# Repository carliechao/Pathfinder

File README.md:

# Pathfinder - Memory Game
starter project and my first repo
this project is a game that tests your memory by playing leds in sequence and having you to repeat the pattern!

A little into the motivation of why I started this project was because I was interested in robotics but never designed anything myself. I had taken note of hackclub for a while but never decided to actually undertake in any of the programs until one day... My friends and I saw how grim our college apps were at the end of 11th grade and decided soemthing had to be done. To be brief, nothing was done. But I did not want to extinguish the light of the motivation just yet and continued with my project. Some of my disdain is echoed into the memory game where you continously fight the overwhelming torrent of forgetfulness by strengthening your mental fortitude through a trial of memory. 

Similar to the challenge that this memory game presents, the process of designing the board also took had lots of challenges I had to overcome and learn from. I learnt, for example, how to draw schematics, lay out my pcb, and code the thing. I am excited to finally finish up this project and see where this experience will take me next.

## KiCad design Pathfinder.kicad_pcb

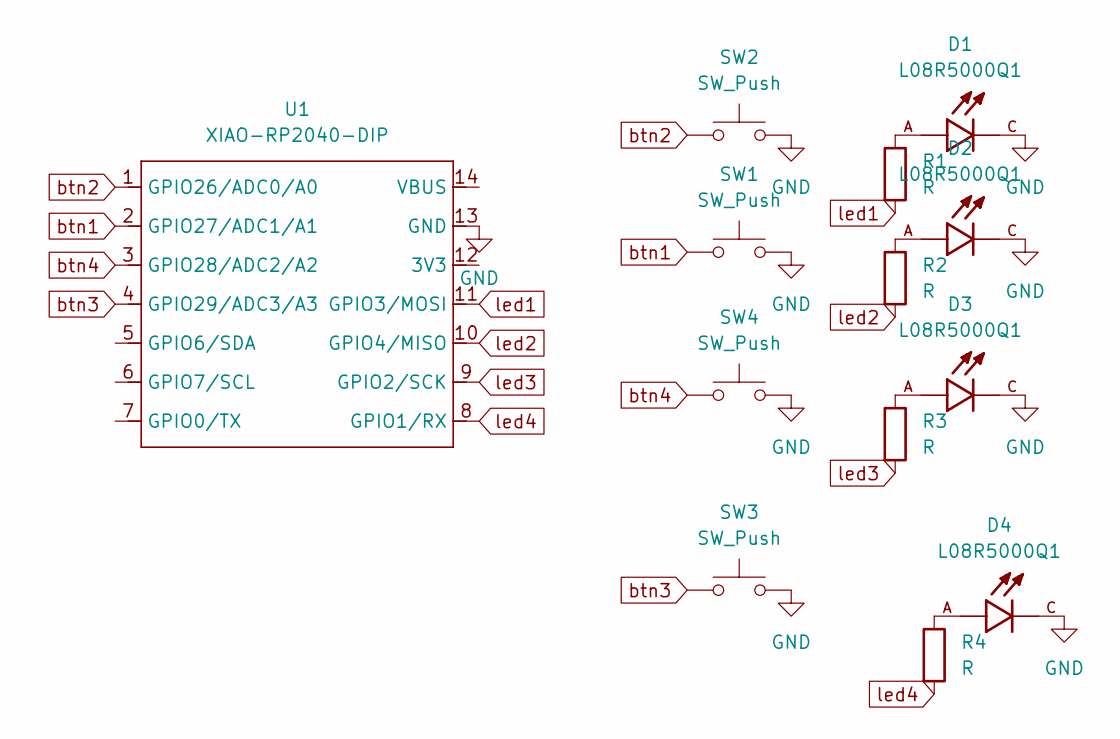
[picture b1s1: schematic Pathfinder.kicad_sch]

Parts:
D1, D2, D3, D4: L08R5000Q1; LEDRD254W57D500H1070; PARTREV NA
R1, R2, R3, R4: R; R_Axial_DIN0207_L6.3mm_D2.5mm_P7.62mm_Horizontal
SW1, SW2, SW3, SW4: SW_Push; SW_Cherry_MX_1.00u_PCB
U1: XIAO-RP2040-DIP

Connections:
GND: D1.C, D2.C, D3.C, D4.C, SW1.2, SW2.2, SW3.2, SW4.2, U1.13 (GND)
unnamed: D1.A, R1.1
unnamed: D2.A, R2.1
unnamed: D3.A, R3.1
unnamed: D4.A, R4.1
btn1: SW1.1, U1.2 (GPIO27/ADC1/A1)
btn2: SW2.1, U1.1 (GPIO26/ADC0/A0)
btn3: SW3.1, U1.4 (GPIO29/ADC3/A3)
btn4: SW4.1, U1.3 (GPIO28/ADC2/A2)
led1: R1.2, U1.11 (GPIO3/MOSI)
led2: R2.2, U1.10 (GPIO4/MISO)
led3: R3.2, U1.9 (GPIO2/SCK)
led4: R4.2, U1.8 (GPIO1/RX)

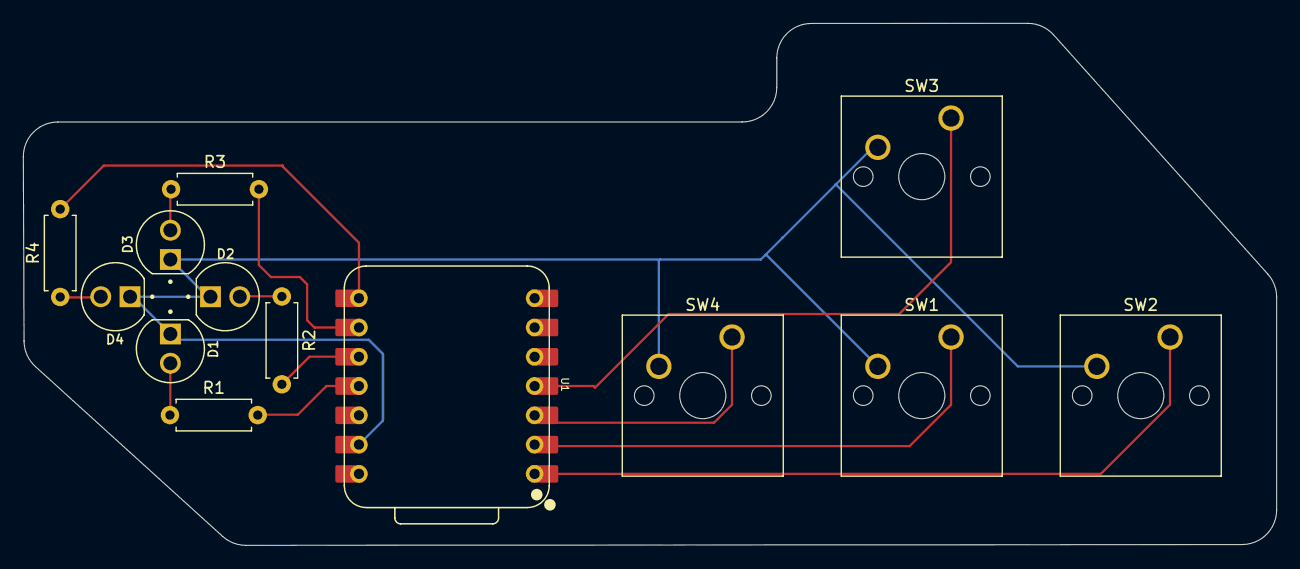
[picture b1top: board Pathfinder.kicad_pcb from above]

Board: 2 copper layers, 108.7 x 45.3 mm, 13 parts (0 on the bottom side), 13 nets.

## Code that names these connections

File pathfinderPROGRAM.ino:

int btns[] = {D1,D0,D3,D2};
int btnsLength = sizeof(btns)/sizeof(btns[0]);
int leds[] = {D10,D9,D8,D7};
int ledsLength = sizeof(leds)/sizeof(leds[0]);
// int led1 = D10;
// int led2 = D9;
// int led3 = D8;
// int led4 = D7;

void setup() {

  for (int i = 0; i < btnsLength; i++){
    pinMode(btns[i], INPUT_PULLUP);
  }

  for (int i = 0; i < ledsLength ; i++){
    pinMode(leds[i], OUTPUT);
  }

  //set a random seed so random is not predictable
  randomSeed(analogRead(A0));
  Serial.begin(9600);
}

int loopNumber = 1;
int ledsLit[50];


void loop() {
  // put your main code here, to run repeatedly:
  //sizeof() = total byes used by the whole array / sizeof(arr[i]) = bytes used by one element
  
   int randIndex = random(0,ledsLength);
   ledsLit[loopNumber-1] = randIndex;

  for (int i = 0; i < loopNumber; i++){
    digitalWrite(leds[ledsLit[i]],HIGH);
    delay(800);
    digitalWrite(leds[ledsLit[i]], LOW);
    delay(200);
  }


  for (int i = 0; i < loopNumber; i++ ){
    bool correct = false;
    unsigned long start = millis();
    //unsigned means that it is a positivie long so it does not
    //reserve space for negative
    while((millis()-start < 3000)&&!correct){
      for (int b = 0; b < btnsLength; b++) {
        if (digitalRead(btns[b]) == LOW) {
          delay(150);
          //low means it is pressed
          //wait for button to be released
          while(digitalRead(btns[b])==LOW){delay(5);}
          if (b == ledsLit[i]) {
            correct = true;
          } else {
            gameOver();
            return;
          }
          break;
        }
      }
    }
    if (!correct){
      gameOver();
      return;
    }
  }
  if (loopNumber<50){
    loopNumber++;
  }
  delay(500);
}

void gameOver(){
  Serial.println("GAME OVER!");
  for (int i = 0; i < 4 ; i++){
    for (int j = 0; j < ledsLength ; j++){
    digitalWrite(leds[j], HIGH);
    }
    delay(200);
    for (int j = 0; j < ledsLength ; j++){
    digitalWrite(leds[j], LOW);
    }
    delay(200);
  }
  loopNumber=1;
  Serial.println("GAME START!");
}

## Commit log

2026-04-23 3D Models
